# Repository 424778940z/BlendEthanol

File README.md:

# Project BlendEthanol
This a collection of my personal PCB designs (mainly microcontrollers)

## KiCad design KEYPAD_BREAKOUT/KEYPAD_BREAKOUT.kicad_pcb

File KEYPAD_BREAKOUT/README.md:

# KEYPAD_BREAKOUT

Breakout board for KailH PG1511 key switches, with back mounted SK6812MINI RGB LED

## Pictures

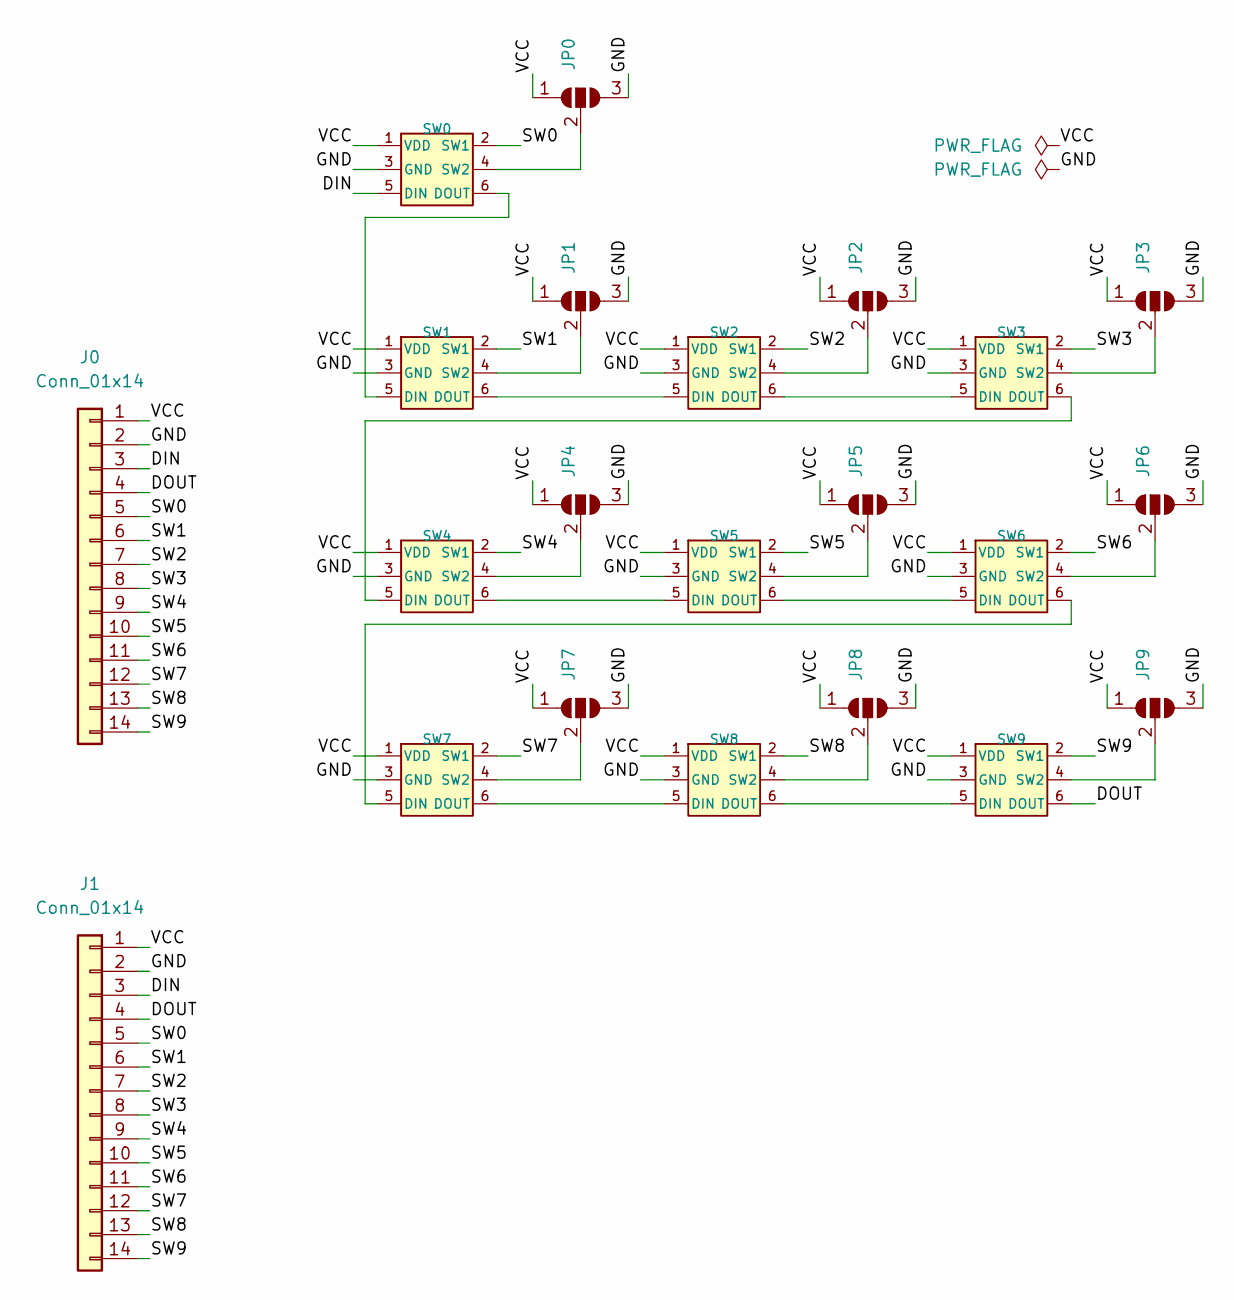
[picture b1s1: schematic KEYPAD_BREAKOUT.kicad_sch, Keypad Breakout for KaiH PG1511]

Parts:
J0: Conn_01x14; PinHeader_1x14_P2.54mm_Horizontal
J1: Conn_01x14; PinSocket_2x07_P2.00mm_Vertical_SMD
JP0, JP1, JP2, JP3, JP4, JP5, JP6, JP7, JP8, JP9: SolderJumper_3_Open; SolderJumper-3_P2.0mm_Open_TrianglePad1.0x1.5mm
SW0, SW1, SW2, SW3, SW4, SW5, SW6, SW7, SW8, SW9: SW_RGB; PG1511B_CPG1511B01D03_EMB_RGB_BACK

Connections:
/DIN: J0.3, J1.3, SW0.5 (DIN)
/DOUT: J0.4, J1.4, SW9.6 (DOUT)
/GND: J0.2, J1.2, JP0.3 (B), JP1.3 (B), JP2.3 (B), JP3.3 (B), JP4.3 (B), JP5.3 (B), JP6.3 (B), JP7.3 (B), JP8.3 (B), JP9.3 (B), SW0.3 (GND), SW1.3 (GND), SW2.3 (GND), SW3.3 (GND), SW4.3 (GND), SW5.3 (GND), SW6.3 (GND), SW7.3 (GND), SW8.3 (GND), SW9.3 (GND)
/SW0: J0.5, J1.5, SW0.2 (SW1)
/SW1: J0.6, J1.6, SW1.2 (SW1)
/SW2: J0.7, J1.7, SW2.2 (SW1)
/SW3: J0.8, J1.8, SW3.2 (SW1)
/SW4: J0.9, J1.9, SW4.2 (SW1)
/SW5: J0.10, J1.10, SW5.2 (SW1)
/SW6: J0.11, J1.11, SW6.2 (SW1)
/SW7: J0.12, J1.12, SW7.2 (SW1)
/SW8: J0.13, J1.13, SW8.2 (SW1)
/SW9: J0.14, J1.14, SW9.2 (SW1)
/VCC: J0.1, J1.1, JP0.1 (A), JP1.1 (A), JP2.1 (A), JP3.1 (A), JP4.1 (A), JP5.1 (A), JP6.1 (A), JP7.1 (A), JP8.1 (A), JP9.1 (A), SW0.1 (VDD), SW1.1 (VDD), SW2.1 (VDD), SW3.1 (VDD), SW4.1 (VDD), SW5.1 (VDD), SW6.1 (VDD), SW7.1 (VDD), SW8.1 (VDD), SW9.1 (VDD)
unnamed: JP0.2 (C), SW0.4 (SW2)
unnamed: JP1.2 (C), SW1.4 (SW2)
unnamed: JP2.2 (C), SW2.4 (SW2)
unnamed: JP3.2 (C), SW3.4 (SW2)
unnamed: JP4.2 (C), SW4.4 (SW2)
unnamed: JP5.2 (C), SW5.4 (SW2)
unnamed: JP6.2 (C), SW6.4 (SW2)
unnamed: JP7.2 (C), SW7.4 (SW2)
unnamed: JP8.2 (C), SW8.4 (SW2)
unnamed: JP9.2 (C), SW9.4 (SW2)
unnamed: SW0.6 (DOUT), SW1.5 (DIN)
unnamed: SW1.6 (DOUT), SW2.5 (DIN)
unnamed: SW2.6 (DOUT), SW3.5 (DIN)
unnamed: SW3.6 (DOUT), SW4.5 (DIN)
unnamed: SW4.6 (DOUT), SW5.5 (DIN)
unnamed: SW5.6 (DOUT), SW6.5 (DIN)
unnamed: SW6.6 (DOUT), SW7.5 (DIN)
unnamed: SW7.6 (DOUT), SW8.5 (DIN)
unnamed: SW8.6 (DOUT), SW9.5 (DIN)

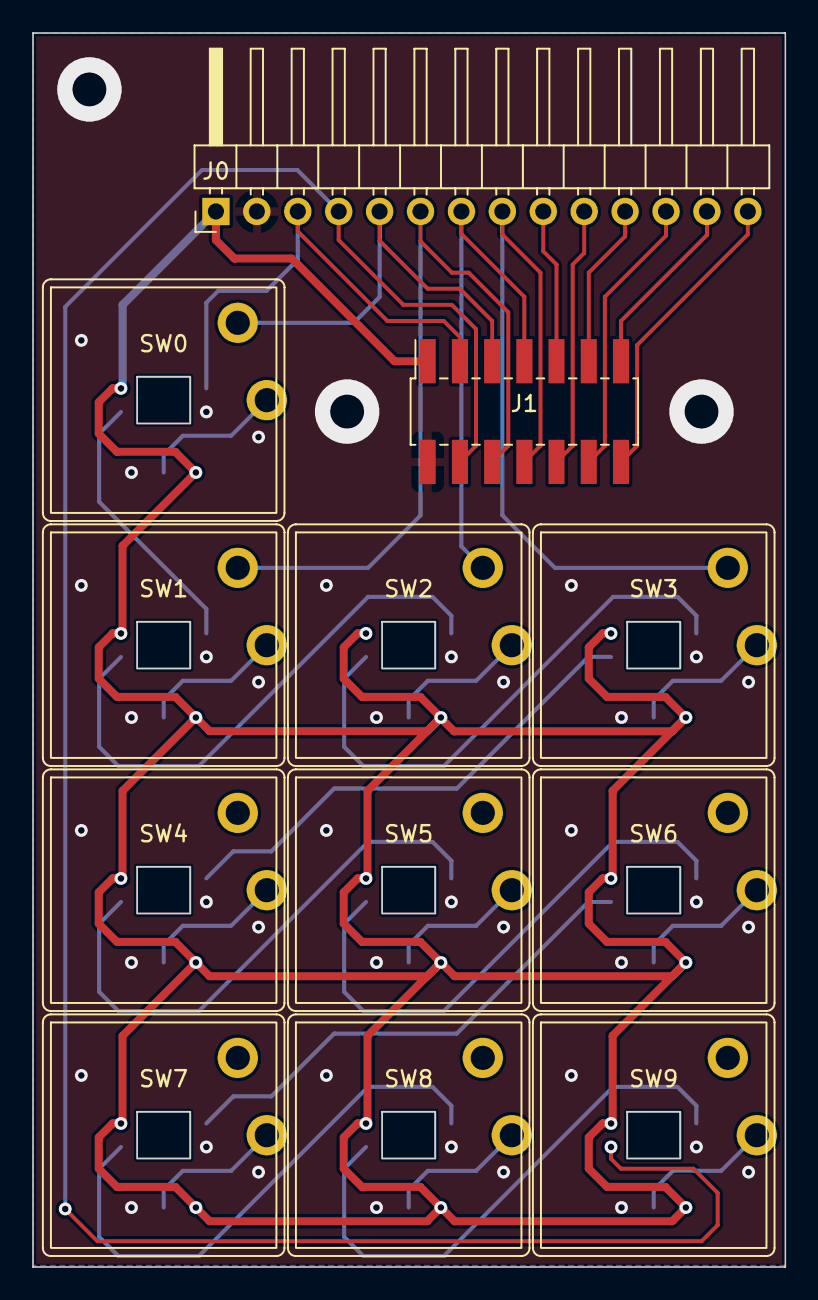
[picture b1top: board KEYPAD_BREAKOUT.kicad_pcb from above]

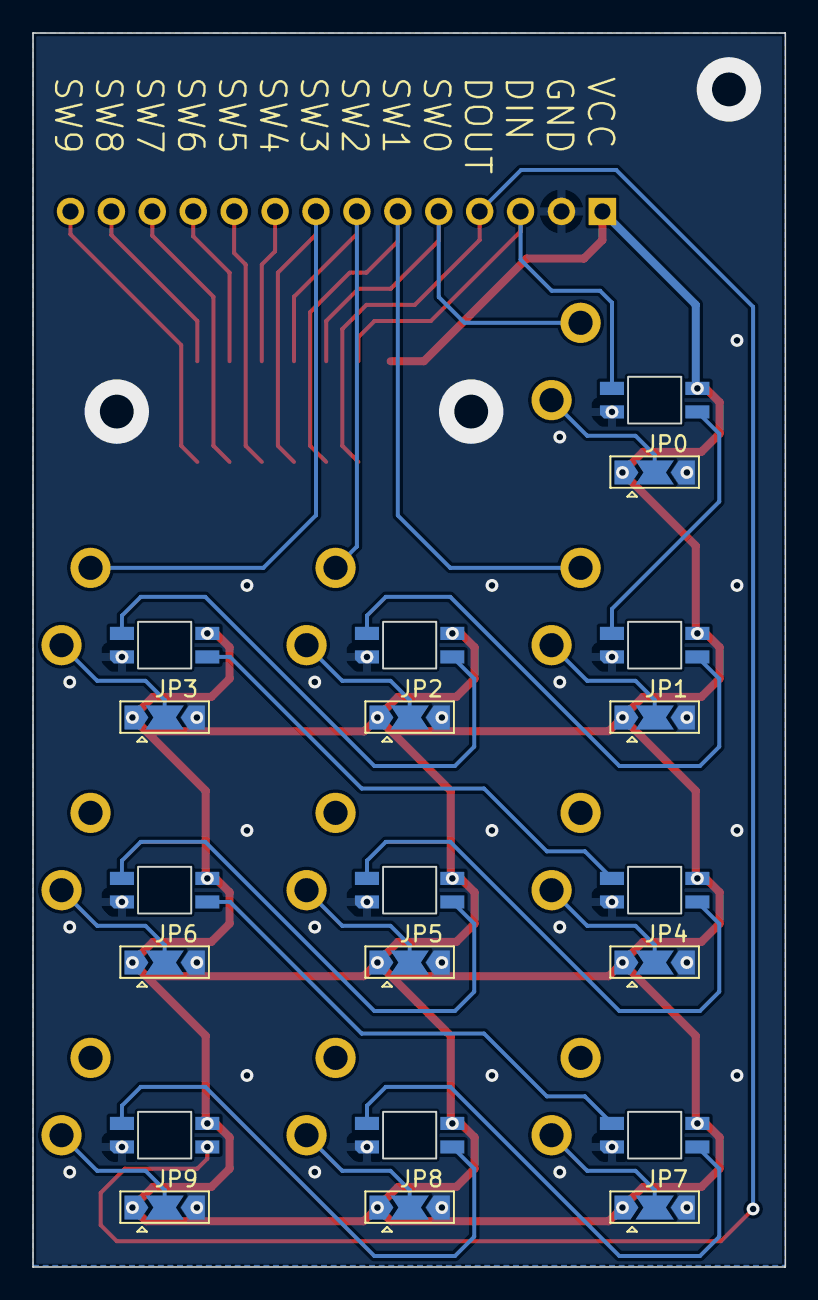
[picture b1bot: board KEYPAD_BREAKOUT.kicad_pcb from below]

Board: 4 copper layers, 46.7 x 76.6 mm, 22 parts (10 on the bottom side), 33 nets.

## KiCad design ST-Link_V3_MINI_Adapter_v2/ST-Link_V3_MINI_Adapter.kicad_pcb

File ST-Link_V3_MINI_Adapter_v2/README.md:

# ST-Link_V3_MINI_Adapter

Very simple board made to convert STDC14 on ST-Link V3 to following standards:
1. Cortex Debug ETM 20P (well ETM pins are not connected)
2. Cortex Debug 10P
3. ST Nucleo 6P
4. Blue/Black Pill 4P + 2P (nReset and SWO)

## Pictures

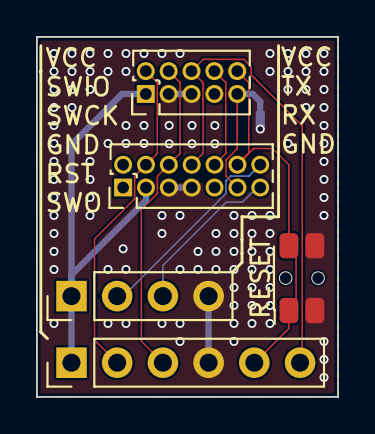
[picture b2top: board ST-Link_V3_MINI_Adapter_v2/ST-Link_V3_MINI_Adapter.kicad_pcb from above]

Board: 2 copper layers, 16.7 x 20.0 mm, 6 parts (1 on the bottom side), 10 nets.

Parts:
J1: Conn_02x07_Odd_Even; PinHeader_2x07_P1.27mm_Vertical
J3: Conn_02x05_Odd_Even; PinHeader_2x05_P1.27mm_Vertical
J4: Conn_01x04; PinHeader_1x04_P2.54mm_Vertical
J5: Conn_01x06; PinHeader_1x06_P2.54mm_Vertical
SW1: SW_Push; SW_SPST_EVQP7C
TIE1: NetTie; NetTie-2_SMD_Pad0.5mm

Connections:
/GND: J1.5, J1.7, J3.3, J3.5, J4.4, J5.4, SW1.2, TIE1.2
/GND_DETECT: J1.11, J3.9, TIE1.1
/NC_TDI: J1.10, J3.8
/RX: J1.13, J4.3
/SWDCLK_TCLK: J1.6, J3.4, J5.3
/SWDIO_TMS: J1.4, J3.2, J5.2
/SWO_TDO: J1.8, J3.6, J5.6
/TX: J1.14, J4.2
/VCC: J1.3, J3.1, J4.1, J5.1
/nRESET: J1.12, J3.10, J5.5, SW1.1

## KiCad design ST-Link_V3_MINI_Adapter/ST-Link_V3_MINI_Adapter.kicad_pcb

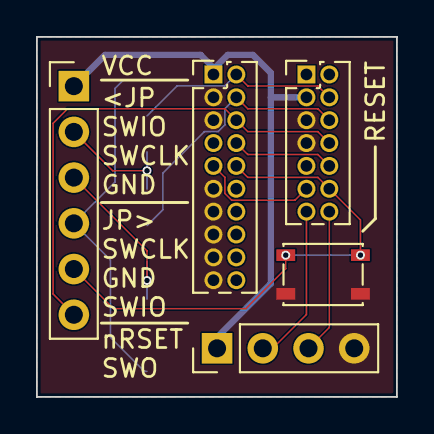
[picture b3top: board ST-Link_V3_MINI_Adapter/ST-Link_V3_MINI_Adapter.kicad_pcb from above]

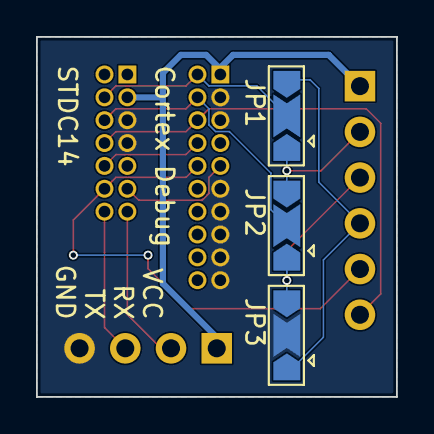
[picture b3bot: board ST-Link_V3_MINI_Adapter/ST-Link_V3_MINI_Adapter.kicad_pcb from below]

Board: 2 copper layers, 20.0 x 20.0 mm, 8 parts (3 on the bottom side), 13 nets.

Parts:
J1: Conn_02x07_Odd_Even; PinHeader_2x07_P1.27mm_Vertical
J2: Conn_02x10_Odd_Even; PinHeader_2x10_P1.27mm_Vertical
J4: Conn_01x04; PinHeader_1x04_P2.54mm_Vertical
J5: Conn_01x06; PinHeader_1x06_P2.54mm_Vertical
JP1, JP2, JP3: SolderJumper_3_Open; SolderJumper-3_P2.0mm_Open_TrianglePad1.0x1.5mm
SW1: SW_Push; SW_SPST_PTS810

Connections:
/GND: J1.5, J1.7, J2.3, J2.5, J2.11, J2.13, J2.15, J2.17, J2.19, J4.4, JP3.2 (C), SW1.2
/GND_DETECT: J1.11, J2.9
/HEADER_2: J5.2, JP1.1 (A), JP2.3 (B)
/HEADER_3: J5.3, JP2.1 (A), JP3.3 (B)
/HEADER_4: J5.4, JP1.3 (B), JP3.1 (A)
/NC_TDI: J1.10, J2.8
/RX: J1.13, J4.2
/SWDCLK_TCLK: J1.6, J2.4, JP2.2 (C)
/SWDIO_TMS: J1.4, J2.2, JP1.2 (C)
/SWO_TDO: J1.8, J2.6, J5.6
/TX: J1.14, J4.3
/VCC: J1.3, J2.1, J4.1, J5.1
/nRESET: J1.12, J2.10, J5.5, SW1.1

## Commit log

2022-10-11 [CORE_ESP32S3U_NGFF_KEY_E] Added to repo
2022-10-11 [CORE_ESP32S3U_NGFF_KEY_E] Fixed readme pictures
2022-10-11 [ST-Link_V3_MINI_Adapter] Added to repo
2022-10-11 [ST-Link_V3_MINI_Adapter] Minor pcb size and copper fill adjust
2022-10-11 Added kikit config file
2022-10-11 [ST-Link_V3_MINI_Adapter] Added reademe and pictures
2022-10-11 [KEYPAD_BREAKOUT] Minor trace adjust, readme update
2022-10-11 Updated .gitignore
2022-10-11 [KEYPAD_BREAKOUT] Added to repo
2022-10-13 [CORE_ESP32S3U_NGFF_KEY_E] Changed all global label to net label in sch
2025-03-14 [ST-Link_V3_MINI_Adapter_v2] Added to repo
2025-03-14 [KEYPAD_BREAKOUT] Added document and 3d models
2025-03-14 [KEYPAD_BREAKOUT] Version 1 release, multiple fixes
